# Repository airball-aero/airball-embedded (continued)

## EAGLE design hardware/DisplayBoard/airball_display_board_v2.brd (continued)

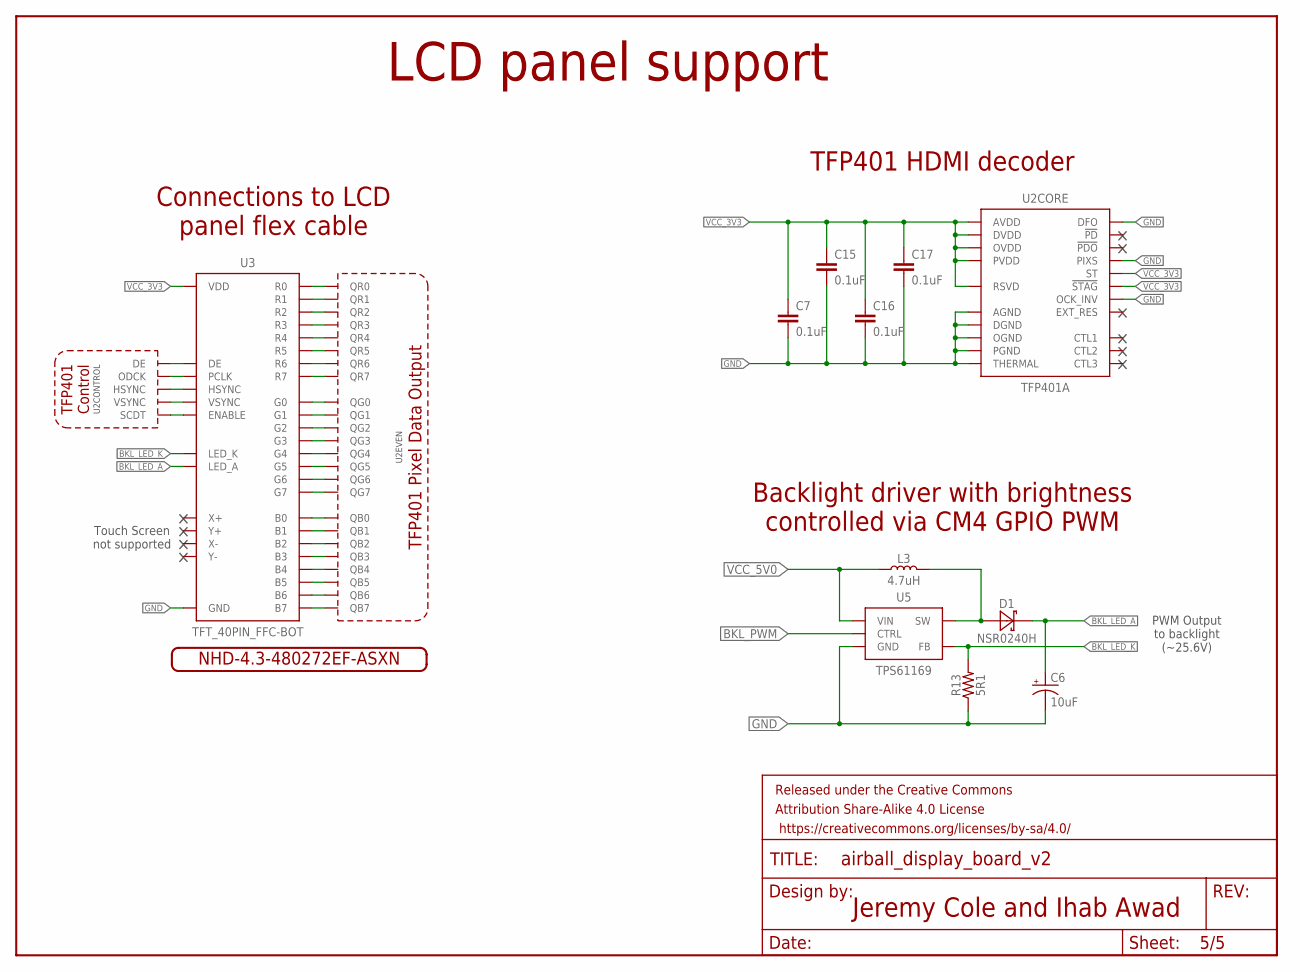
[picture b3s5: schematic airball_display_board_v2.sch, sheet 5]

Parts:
C6: 10uF; EIA3216
C7, C15, C16, C17: 0.1uF; 0603
D1: NSR0240H; SOD323
FRAME5: FRAME-LETTER; CREATIVE_COMMONS
L3: 4.7uH; INDUCTOR_SMD_4X4MM
R13: 5R1; 0603
U2: TFP401A; TQFP100_POWER_LITE
U3: TFT_40PIN_FFC-BOT; HIROSE_FFC40_FH12-40S-0.5SH
U5: TPS61169; SOT353-5
U$4: NHD-4.3-480272EF-ASXN

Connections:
B0: U2.10 (QB0), U3.21 (B0)
B1: U2.11 (QB1), U3.22 (B1)
B2: U2.12 (QB2), U3.23 (B2)
B3: U2.13 (QB3), U3.24 (B3)
B4: U2.14 (QB4), U3.25 (B4)
B5: U2.15 (QB5), U3.26 (B5)
B6: U2.16 (QB6), U3.27 (B6)
B7: U2.17 (QB7), U3.28 (B7)
BKL_LED_A: C6.+, D1.K (C), U3.2 (LED_A)
BKL_LED_K: R13.2, U3.1 (LED_K), U5.3 (FB)
BKL_PWM: U5.4 (CTRL); also elsewhere on the board
DE: U2.46 (DE), U3.34 (DE)
G0: U2.20 (QG0), U3.13 (G0)
G1: U2.21 (QG1), U3.14 (G1)
G2: U2.22 (QG2), U3.15 (G2)
G3: U2.23 (QG3), U3.16 (G3)
G4: U2.24 (QG4), U3.17 (G4)
G5: U2.25 (QG5), U3.18 (G5)
G6: U2.26 (QG6), U3.19 (G6)
G7: U2.27 (QG7), U3.20 (G7)
GND: C6.-, C7.2, C15.2, C16.2, C17.2, R13.1, U2.1 (DFO), U2.4 (PIXS), U2.5 (DGND), U2.19 (OGND), U2.28 (OGND), U2.39 (DGND), U2.45 (OGND), U2.58 (OGND), U2.68 (DGND), U2.76 (OGND), U2.79 (AGND), U2.83 (AGND), U2.87 (AGND), U2.89 (AGND), U2.92 (AGND), U2.98 (PGND), U2.100 (OCK_INV), U2.TH21 (THERMAL), U2.TH22 (THERMAL), U2.TH23 (THERMAL), U2.TH24 (THERMAL), U2.TH25 (THERMAL), U2.TH30 (THERMAL), U2.TH34 (THERMAL), U2.TH39 (THERMAL), U2.TH43 (THERMAL), U2.TH48 (THERMAL), U2.TH52 (THERMAL), U2.TH57 (THERMAL), U2.TH58 (THERMAL), U2.TH59 (THERMAL), U2.TH60 (THERMAL), U2.TH61 (THERMAL), U2.THA (THERMAL), U2.THB (THERMAL), U3.3 (GND), U3.29 (GND), U3.36 (GND), U5.2 (GND); also elsewhere on the board
HSYNC: U2.48 (HSYNC), U3.32 (HSYNC)
L_BKL: D1.A, L3.2, U5.1 (SW)
PCLK: U2.44 (ODCK), U3.30 (PCLK)
R0: U2.30 (QR0), U3.5 (R0)
R1: U2.31 (QR1), U3.6 (R1)
R2: U2.32 (QR2), U3.7 (R2)
R3: U2.33 (QR3), U3.8 (R3)
R4: U2.34 (QR4), U3.9 (R4)
R5: U2.35 (QR5), U3.10 (R5)
R6: U2.36 (QR6), U3.11 (R6)
R7: U2.37 (QR7), U3.12 (R7)
SCDT: U2.8 (SCDT), U3.31 (ENABLE)
VCC_3V3: C7.1, C15.1, C16.1, C17.1, U2.3 (ST), U2.6 (DVDD), U2.7 (!STAG), U2.18 (OVDD), U2.29 (OVDD), U2.38 (DVDD), U2.43 (OVDD), U2.57 (OVDD), U2.67 (DVDD), U2.78 (OVDD), U2.82 (AVDD), U2.84 (AVDD), U2.88 (AVDD), U2.95 (AVDD), U2.97 (PVDD), U2.99 (RSVD), U3.4 (VDD); also elsewhere on the board
VCC_5V0: L3.1, U5.5 (VIN); also elsewhere on the board
VSYNC: U2.47 (VSYNC), U3.33 (VSYNC)

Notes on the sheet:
Jeremy Cole and Ihab Awad
Touch Screen not supported
PWM Output to backlight (~25.6V)
LCD panel support
Connections to LCD panel flex cable
Backlight driver with brightness controlled via CM4 GPIO PWM
TFP401 HDMI decoder

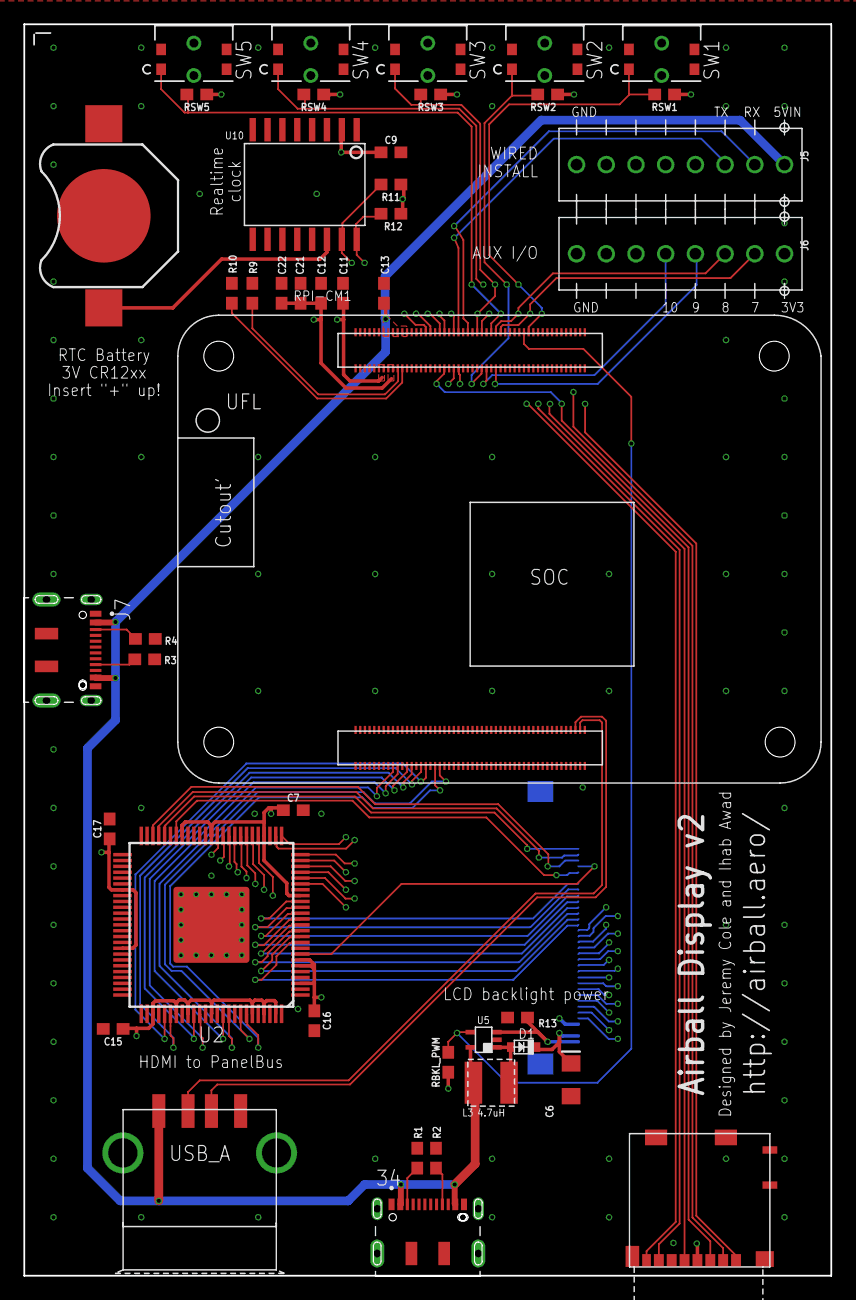
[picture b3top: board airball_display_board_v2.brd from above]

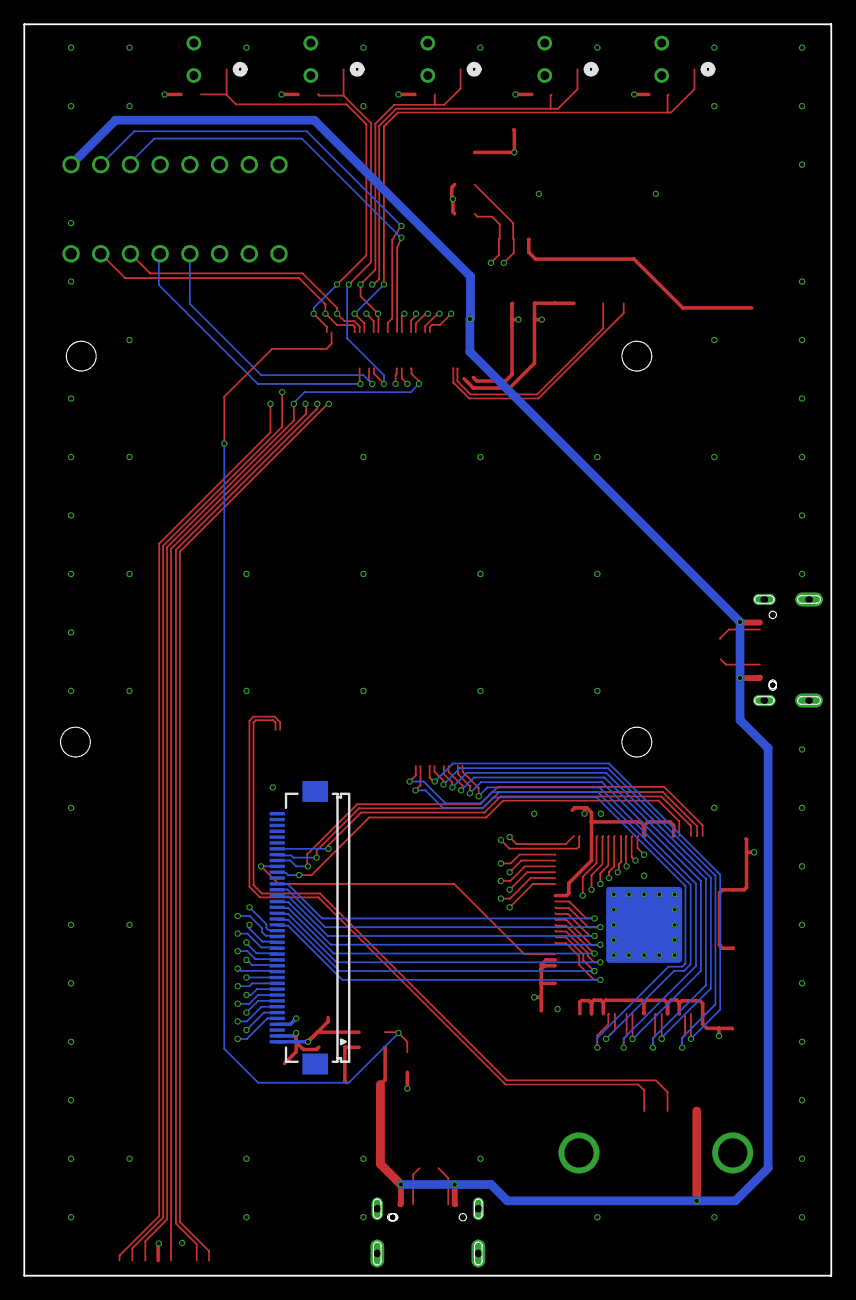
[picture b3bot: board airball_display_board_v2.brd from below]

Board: 4 copper layers, 69.0 x 107.0 mm, 51 parts (2 on the bottom side), 73 nets.

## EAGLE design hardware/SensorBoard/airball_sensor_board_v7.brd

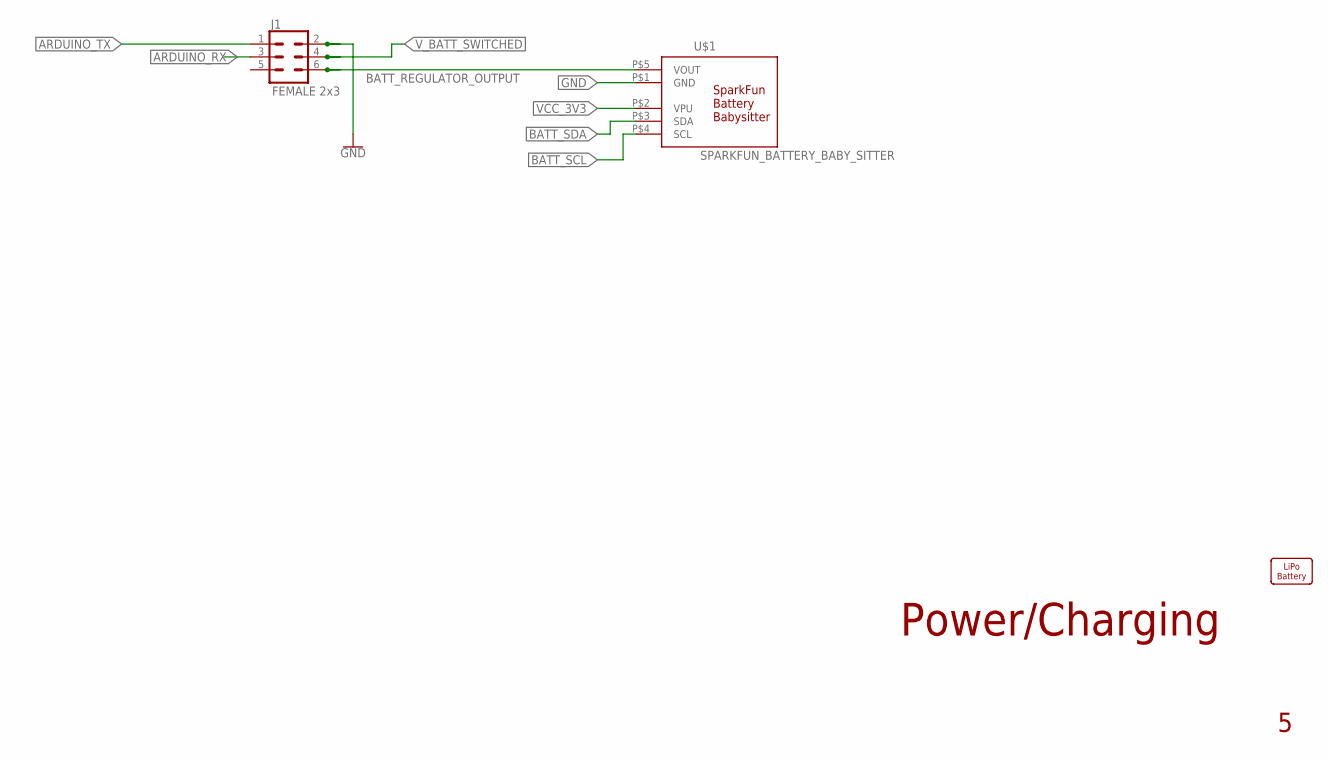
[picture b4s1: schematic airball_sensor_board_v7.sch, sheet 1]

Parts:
J1: FEMALE 2x3; 2X3
U$1: SPARKFUN_BATTERY_BABY_SITTER
U$3: LIPO_BATTERY_OUTLINE-1000MAH; SPARKFUN_LIPO_1000MAH

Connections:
ARDUINO_RX: J1.3; also elsewhere on the board
ARDUINO_TX: J1.1; also elsewhere on the board
BATT_REGULATOR_OUTPUT: J1.6, U$1.P$5 (VOUT)
BATT_SCL: U$1.P$4 (SCL); also elsewhere on the board
BATT_SDA: U$1.P$3 (SDA); also elsewhere on the board
GND: J1.2, U$1.P$1 (GND); also elsewhere on the board
VCC_3V3: U$1.P$2 (VPU); also elsewhere on the board
V_BATT_SWITCHED: J1.4; also elsewhere on the board

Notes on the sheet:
Power/Charging

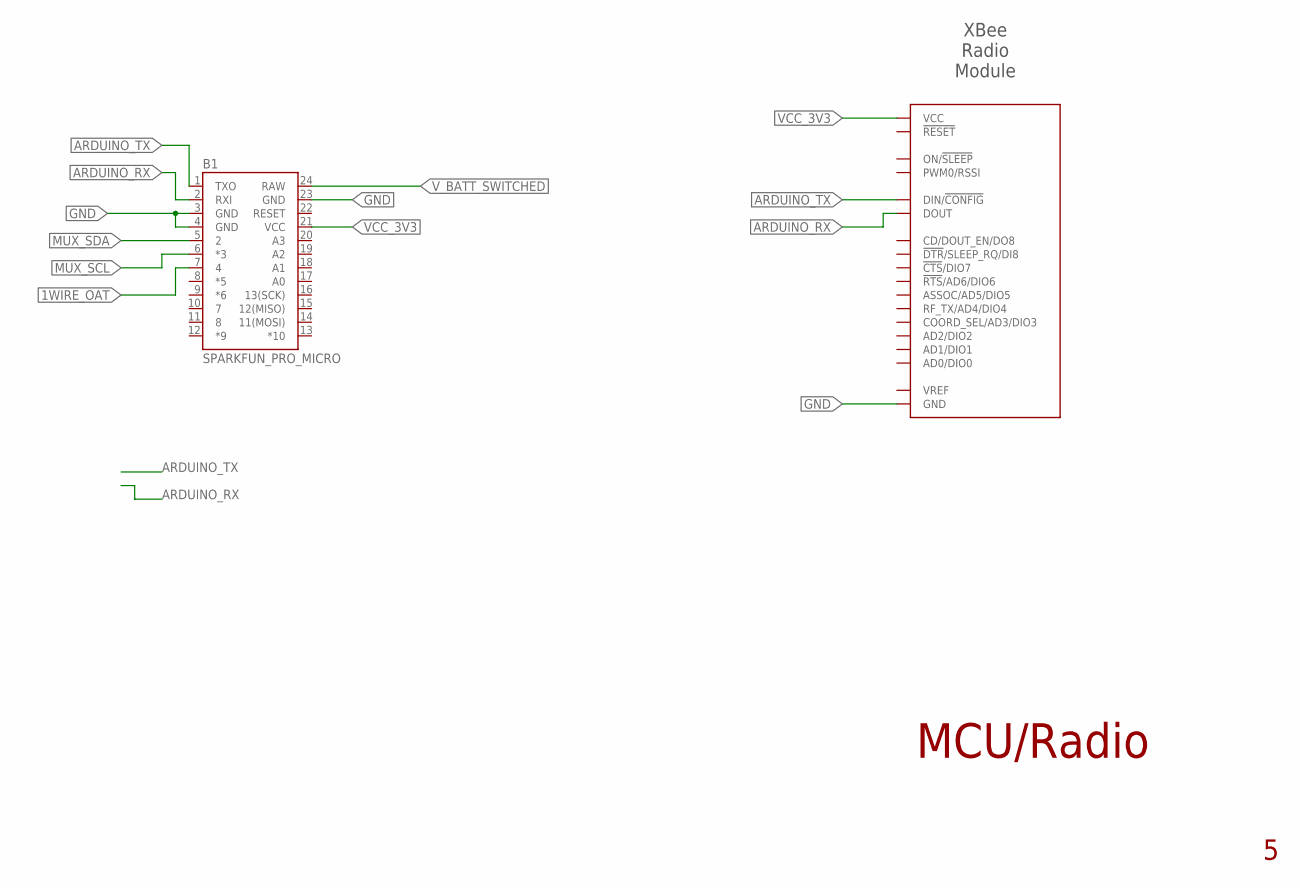
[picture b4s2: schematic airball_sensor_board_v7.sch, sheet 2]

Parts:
B1: SPARKFUN_PRO_MICRO
XBEE: XBEE-PRO-SMD

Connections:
1WIRE_OAT: B1.7 (4); also elsewhere on the board
ARDUINO_RX: B1.2 (RXI), XBEE.2 (DOUT); also elsewhere on the board
ARDUINO_TX: B1.1 (TXO), XBEE.3 (DIN/!CONFIG); also elsewhere on the board
GND: B1.3 (GND), B1.4 (GND), B1.23 (GND), XBEE.10 (GND); also elsewhere on the board
MUX_SCL: B1.6 (*3); also elsewhere on the board
MUX_SDA: B1.5 (2); also elsewhere on the board
VCC_3V3: B1.21 (VCC), XBEE.1 (VCC); also elsewhere on the board
V_BATT_SWITCHED: B1.24 (RAW); also elsewhere on the board

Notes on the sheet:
XBee Radio Module
MCU/Radio

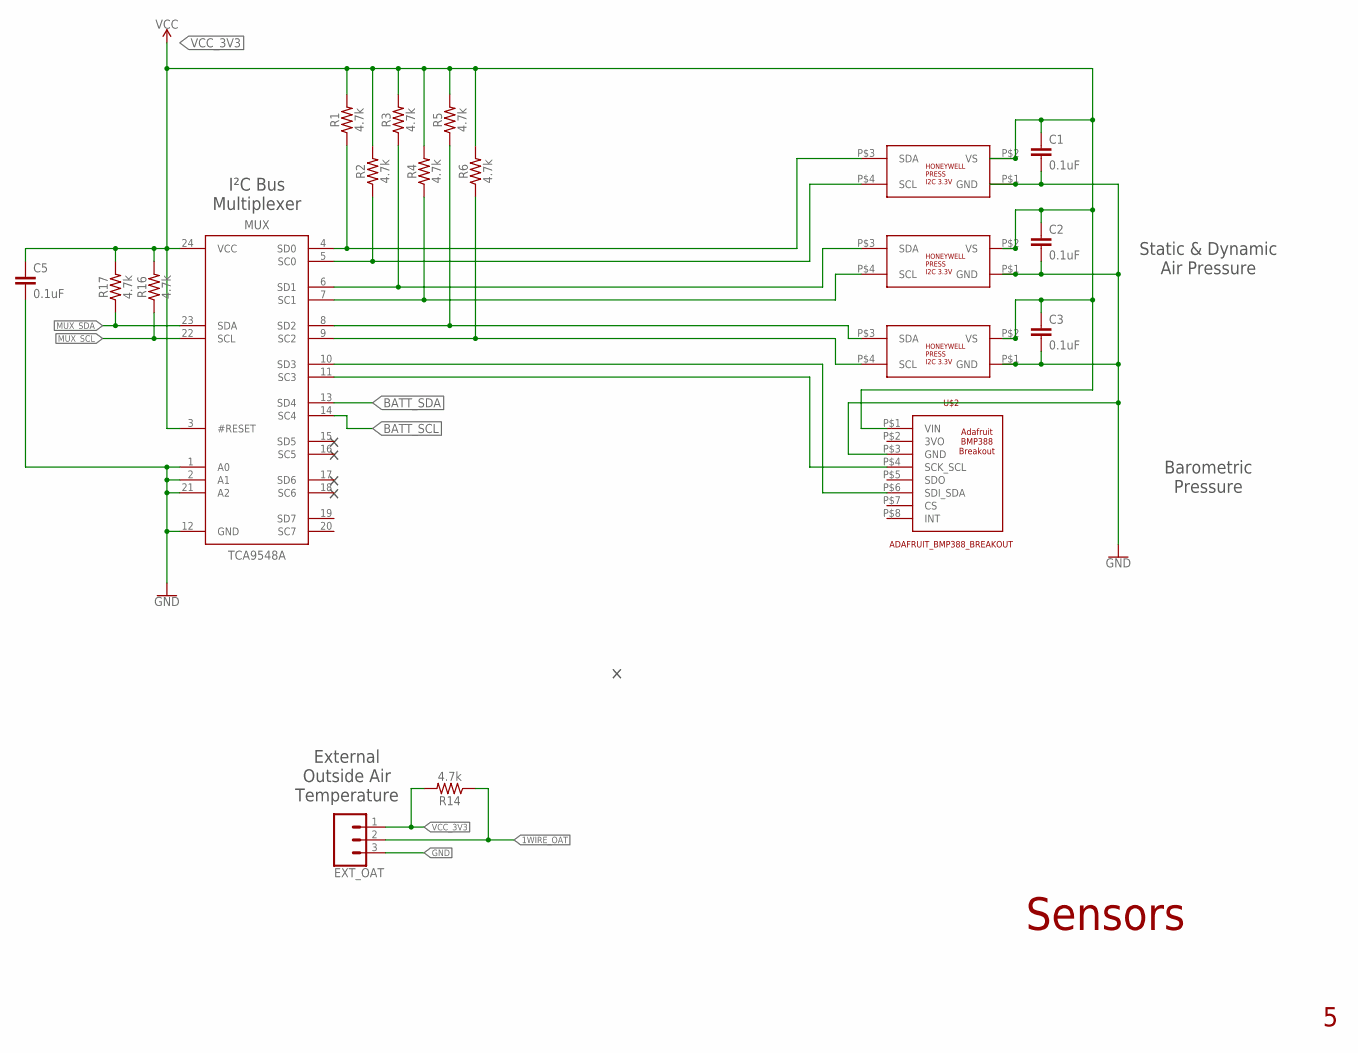
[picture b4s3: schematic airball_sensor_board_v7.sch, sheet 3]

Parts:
C1, C2, C3, C5: 0.1uF; 0603
DP0: HONEYWELL_TRUSTABILITY_I2C_3.3V; HONEYWELL_TRUSTABILITY_DIP_RR
DPA: HONEYWELL_TRUSTABILITY_I2C_3.3V; HONEYWELL_TRUSTABILITY_DIP_RR
DPB: HONEYWELL_TRUSTABILITY_I2C_3.3V; HONEYWELL_TRUSTABILITY_DIP_RR
EXT_OAT: CONN_03; 1X03
MUX: TCA9548A; TSSOP24
R1, R2, R3, R4, R5, R6, R14, R16, R17: 4.7k; 0603
U$2: ADAFRUIT_BMP388_BREAKOUT

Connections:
1WIRE_OAT: EXT_OAT.2, R14.1; also elsewhere on the board
BATT_SCL: MUX.14 (SC4); also elsewhere on the board
BATT_SDA: MUX.13 (SD4); also elsewhere on the board
GND: C1.2, C2.2, C3.2, C5.2, DP0.P$1 (GND), DPA.P$1 (GND), DPB.P$1 (GND), EXT_OAT.3, MUX.1 (A0), MUX.2 (A1), MUX.12 (GND), MUX.21 (A2), U$2.P$3 (GND); also elsewhere on the board
MUX_SCL: MUX.22 (SCL), R16.1; also elsewhere on the board
MUX_SDA: MUX.23 (SDA), R17.1; also elsewhere on the board
SCL_BMP_BARO: MUX.11 (SC3), U$2.P$4 (SCK_SCL)
SCL_DP0: DP0.P$4 (SCL), MUX.5 (SC0), R2.1
SCL_DPA: DPA.P$4 (SCL), MUX.7 (SC1), R4.1
SCL_DPB: DPB.P$4 (SCL), MUX.9 (SC2), R6.1
SDA_BMP_BARO: MUX.10 (SD3), U$2.P$6 (SDI_SDA)
SDA_DP0: DP0.P$3 (SDA), MUX.4 (SD0), R1.1
SDA_DPA: DPA.P$3 (SDA), MUX.6 (SD1), R3.1
SDA_DPB: DPB.P$3 (SDA), MUX.8 (SD2), R5.1
VCC_3V3: C1.1, C2.1, C3.1, C5.1, DP0.P$2 (VS), DPA.P$2 (VS), DPB.P$2 (VS), EXT_OAT.1, MUX.3 (#RESET), MUX.24 (VCC), R1.2, R2.2, R3.2, R4.2, R5.2, R6.2, R14.2, R16.2, R17.2, U$2.P$1 (VIN); also elsewhere on the board

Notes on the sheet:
Sensors
I²C Bus Multiplexer
Static & Dynamic Air Pressure
External Outside Air Temperature
Barometric Pressure

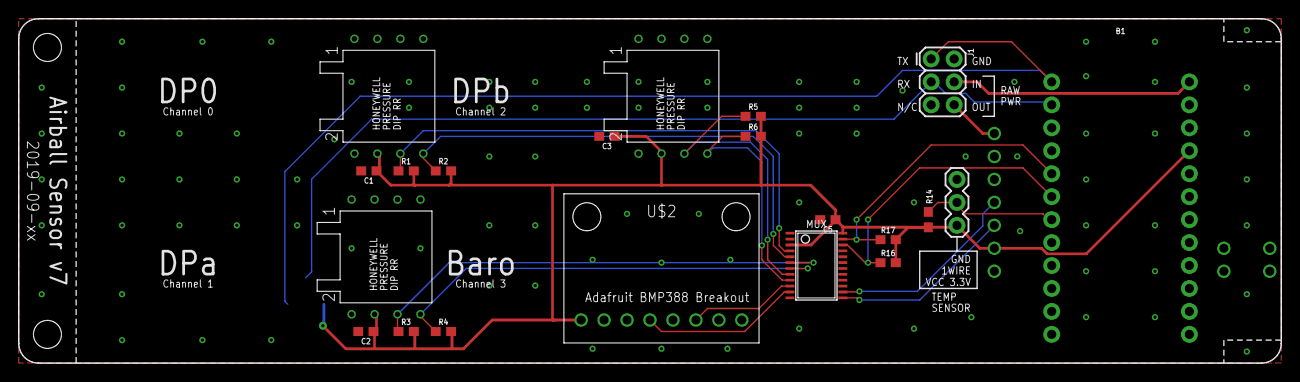
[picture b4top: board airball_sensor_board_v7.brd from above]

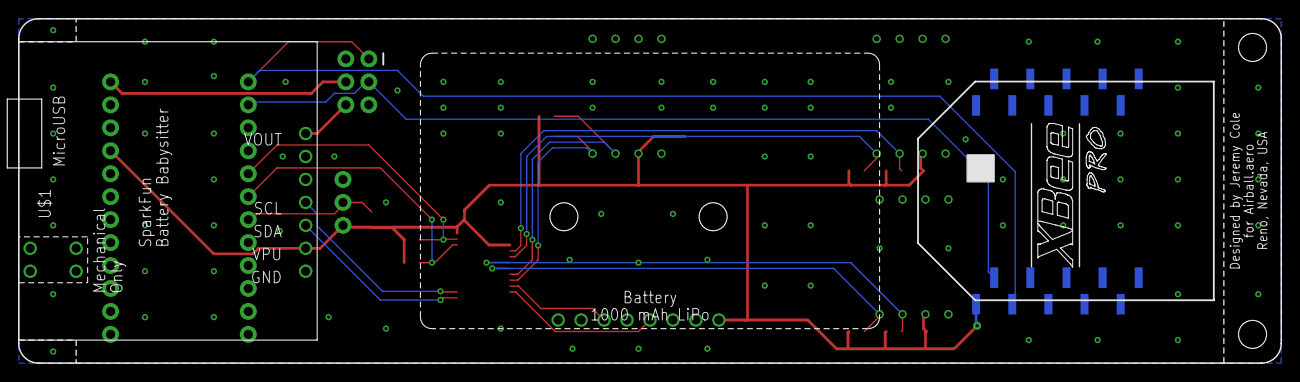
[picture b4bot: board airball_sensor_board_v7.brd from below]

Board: 2 copper layers, 139.7 x 38.1 mm, 24 parts (3 on the bottom side), 19 nets.

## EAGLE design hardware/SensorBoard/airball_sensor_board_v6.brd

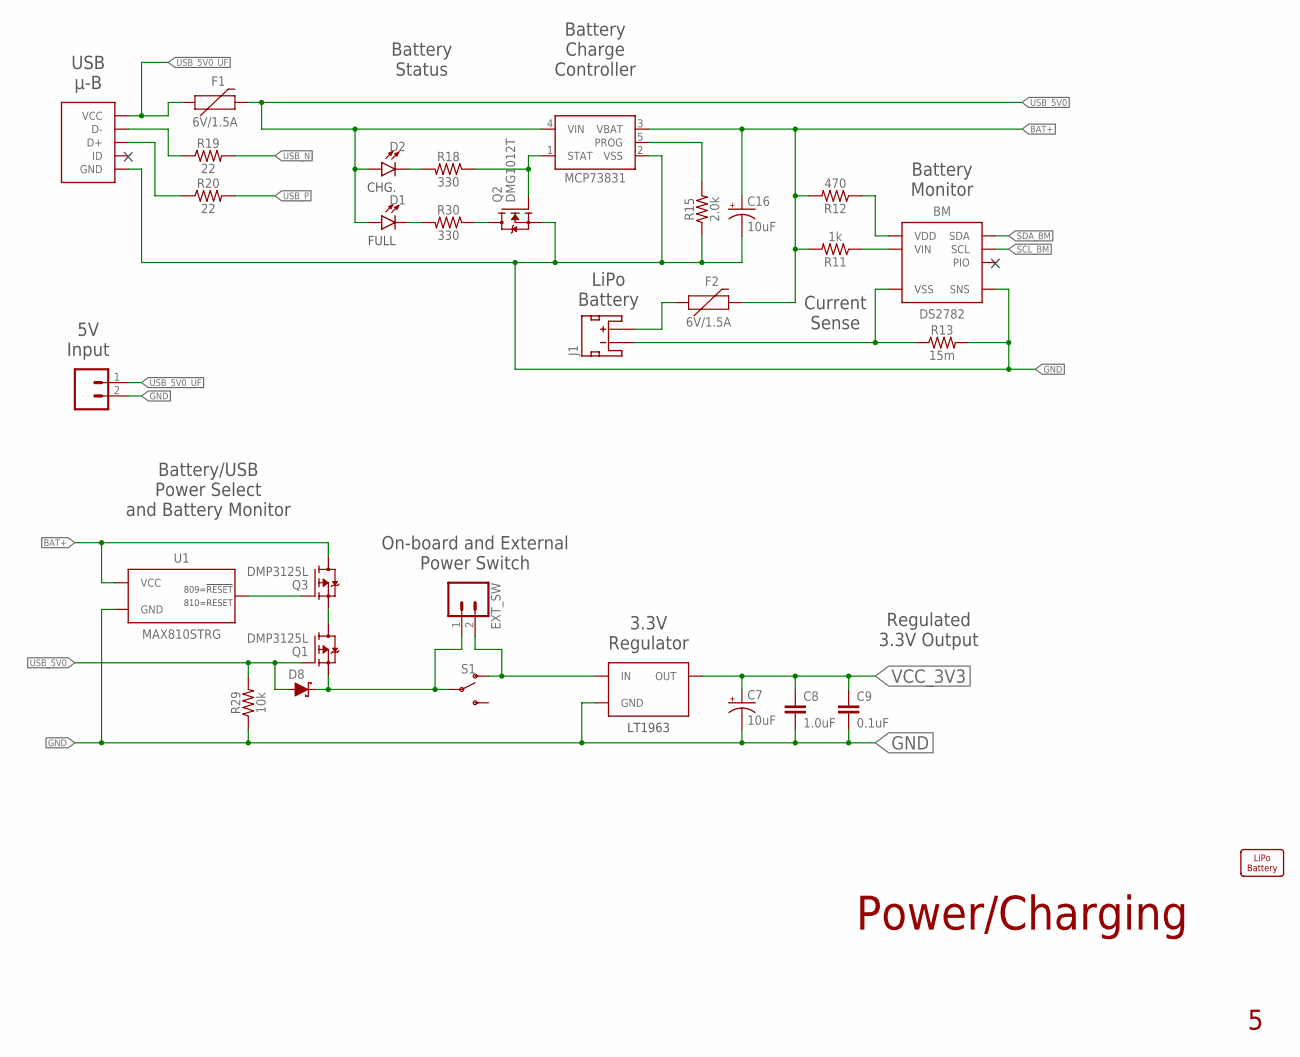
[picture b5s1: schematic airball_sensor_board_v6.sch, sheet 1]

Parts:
BM: DS2782; TSSOP8
C7, C16: 10uF; EIA3216
C8: 1.0uF; 0603
C9: 0.1uF; 0603
CC: MCP73831; SOT23-5
D1, D2: LED0603; LED-0603
D8: DIODE-SCHOTTKY-BAT20J; SOD-323
EXT_POWER: CONN_02; 1X02
EXT_SW: CONN_02; 1X02
F1, F2: 6V/1.5A; 1206
J1: JST_2MM_MALE; JST-2-SMD
JP1: USB_MICROB_PLUG; USB_MICRO_B_TYCO
Q1, Q3: DMP3125L; SOT23-3
Q2: DMG1012T; SOT523-3
R11: 1k; 0603
R12: 470; 0603
R13: 15m; 1206
R15: 2.0k; 0603
R18, R30: 330; 0603
R19, R20: 22; 0603
R29: 10k; 0603
S1: SWITCH-SPDT-SMD-RIGHT-ANGLE; SWITCH_SPST_SMD_A
U1: MAX810STRG; SOT23-3
U$3: LIPO_BATTERY_OUTLINE-1000MAH; SPARKFUN_LIPO_1000MAH
VREG: LT1963; SOT223-3

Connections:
BAT+: C16.+, CC.3 (VBAT), F2.2, Q3.3 (D), R11.2, R12.2, U1.3 (VCC)
BAT+_UF: F2.1, J1.2 (+)
BAT-: BM.2 (VSS), J1.1 (-), R13.1
BAT_LOW: Q3.1 (G), U1.2 (RESET)
BM_VDD: BM.4 (VDD), R12.1
BM_VIN: BM.3 (VIN), R11.1
CC_PROG: CC.5 (PROG), R15.2
GND: BM.7 (SNS), C7.-, C8.2, C9.2, C16.-, CC.2 (VSS), EXT_POWER.2, JP1.5 (GND), JP1.SH@1 (GND), JP1.SH@2 (GND), JP1.SH@3 (GND), JP1.SH@4 (GND), Q2.3 (S), R13.2, R15.1, R29.1, U1.1 (GND), VREG.2 (GND), VREG.TAB (GND); also elsewhere on the board
unnamed: D2.C, R18.2
unnamed: CC.1 (STAT), Q2.1 (G), R18.1
unnamed: Q1.3 (D), Q3.2 (S)
unnamed: D1.C, R30.2
unnamed: Q2.2 (D), R30.1
SCL_BM: BM.6 (SCL); also elsewhere on the board
SDA_BM: BM.5 (SDA); also elsewhere on the board
USB_5V0: CC.4 (VIN), D1.A, D2.A, D8.A, F1.2, Q1.1 (G), R29.2
USB_5V0_UF: EXT_POWER.1, F1.1, JP1.1 (VCC)
USB_N: R19.2; also elsewhere on the board
USB_P: R20.2; also elsewhere on the board
USB_X_N: JP1.2 (D-), R19.1
USB_X_P: JP1.3 (D+), R20.1
VCC_3V3: C7.+, C8.1, C9.1, VREG.3 (OUT); also elsewhere on the board
VIN: D8.C, EXT_SW.1, Q1.2 (S), S1.2
VIN_SW: EXT_SW.2, S1.1 (O), VREG.1 (IN)

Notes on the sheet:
LiPo Battery
USB µ-B
Battery Monitor
3.3V Regulator
Battery Charge Controller
On-board and External Power Switch
Regulated 3.3V Output
Battery Status
Current Sense
Power/Charging
5V Input
CHG.
FULL
Battery/USB Power Select and Battery Monitor

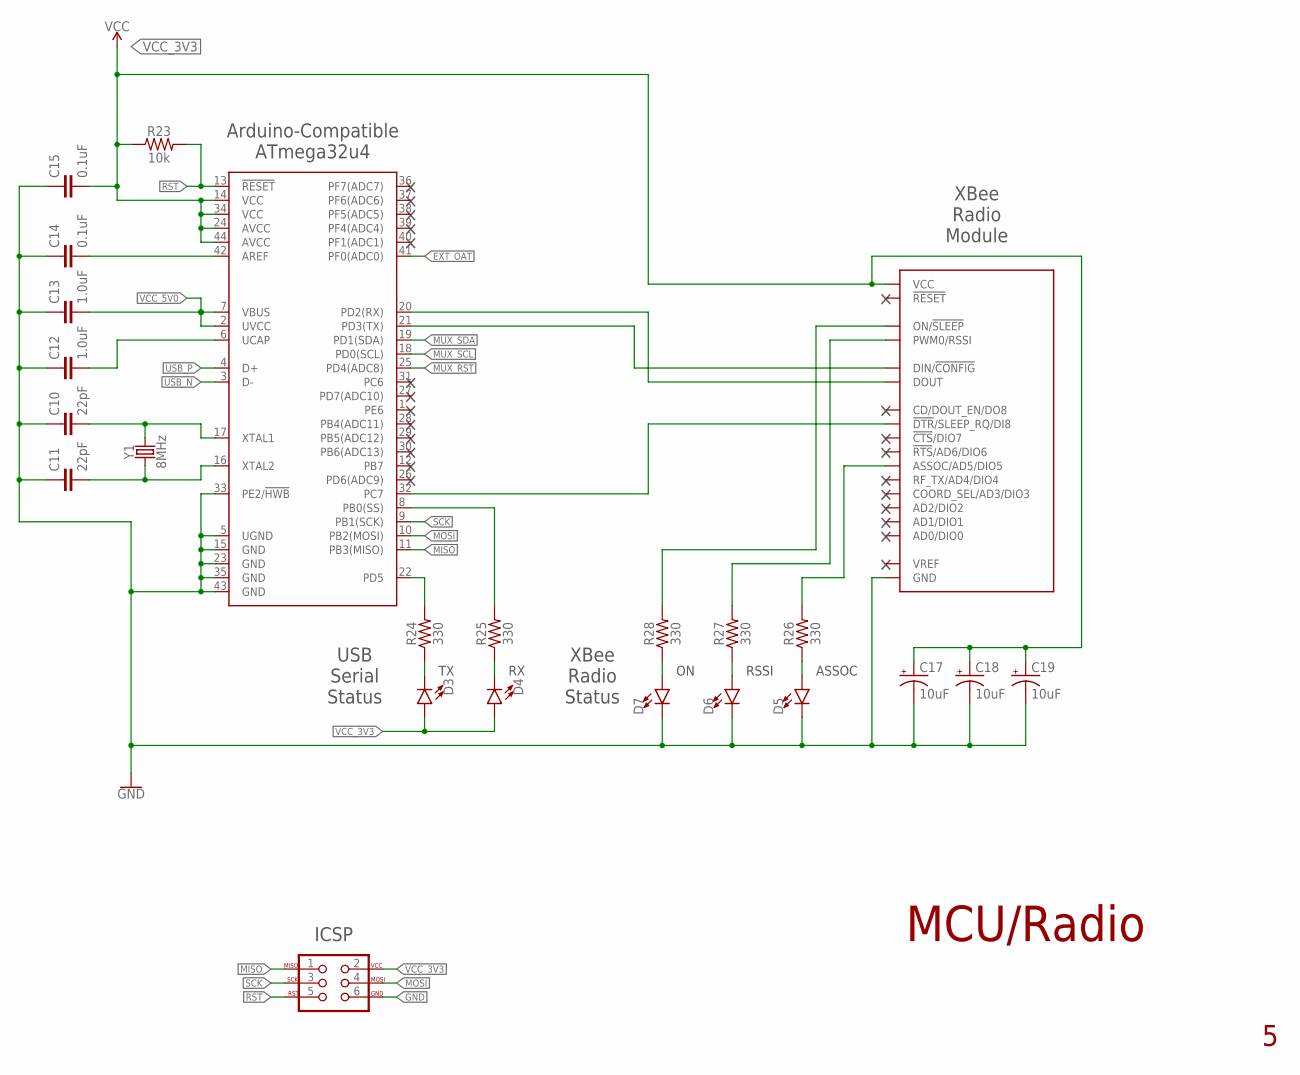
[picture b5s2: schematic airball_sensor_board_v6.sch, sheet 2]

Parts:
C10, C11: 22pF; 0603
C12, C13: 1.0uF; 0603
C14, C15: 0.1uF; 0603
C17, C18, C19: 10uF; EIA3216
D3, D4, D5, D6, D7: LED0603; LED-0603
ICSP: AVR_SPI_PROG_3X2PTH; 2X3
MCU: 32U4; TQFP44
R23: 10k; 0603
R24, R25, R26, R27, R28: 330; 0603
XBEE: XBEE-PRO-SMD
Y1: 8MHz; CRYSTAL-SMD-5X3.2-4PAD

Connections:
ASSOC_LED: R26.2, XBEE.15 (ASSOC/AD5/DIO5)
EXT_OAT: MCU.41 (PF0(ADC0)); also elsewhere on the board
GND: C10.1, C11.1, C12.1, C13.1, C14.1, C15.1, C17.-, C18.-, C19.-, D5.C, D6.C, D7.C, ICSP.6, MCU.5 (UGND), MCU.15 (GND), MCU.23 (GND), MCU.33 (PE2/!HWB), MCU.35 (GND), MCU.43 (GND), XBEE.10 (GND); also elsewhere on the board
MISO: ICSP.1, MCU.11 (PB3(MISO))
MOSI: ICSP.4, MCU.10 (PB2(MOSI))
MUX_RST: MCU.25 (PD4(ADC8)); also elsewhere on the board
MUX_SCL: MCU.18 (PD0(SCL)); also elsewhere on the board
MUX_SDA: MCU.19 (PD1(SDA)); also elsewhere on the board
unnamed: D3.C, R24.1
unnamed: D4.C, R25.1
unnamed: C10.2, MCU.17 (XTAL1), Y1.3 (2)
unnamed: C11.2, MCU.16 (XTAL2), Y1.1
unnamed: C14.2, MCU.42 (AREF)
unnamed: C12.2, MCU.6 (UCAP)
unnamed: D5.A, R26.1
unnamed: D6.A, R27.1
unnamed: D7.A, R28.1
ON_LED: R28.2, XBEE.13 (ON/!SLEEP)
RSSI_LED: R27.2, XBEE.6 (PWM0/RSSI)
RST: ICSP.5, MCU.13 (!RESET), R23.2
RXD: MCU.20 (PD2(RX)), XBEE.2 (DOUT)
RX_LED: MCU.8 (PB0(SS)), R25.2
SCK: ICSP.3, MCU.9 (PB1(SCK))
SLEEP_RQ: MCU.32 (PC7), XBEE.9 (!DTR!/SLEEP_RQ/DI8)
TXD: MCU.21 (PD3(TX)), XBEE.3 (DIN/!CONFIG)
TX_LED: MCU.22 (PD5), R24.2
USB_N: MCU.3 (D-); also elsewhere on the board
USB_P: MCU.4 (D+); also elsewhere on the board
VCC_3V3: C15.2, C17.+, C18.+, C19.+, D3.A, D4.A, ICSP.2, MCU.14 (VCC), MCU.24 (AVCC), MCU.34 (VCC), MCU.44 (AVCC), R23.1, XBEE.1 (VCC); also elsewhere on the board
VCC_5V0: C13.2, MCU.2 (UVCC), MCU.7 (VBUS)

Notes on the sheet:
RSSI
ASSOC
XBee Radio Module
Arduino-Compatible ATmega32u4
ICSP
USB Serial Status
XBee Radio Status
MCU/Radio

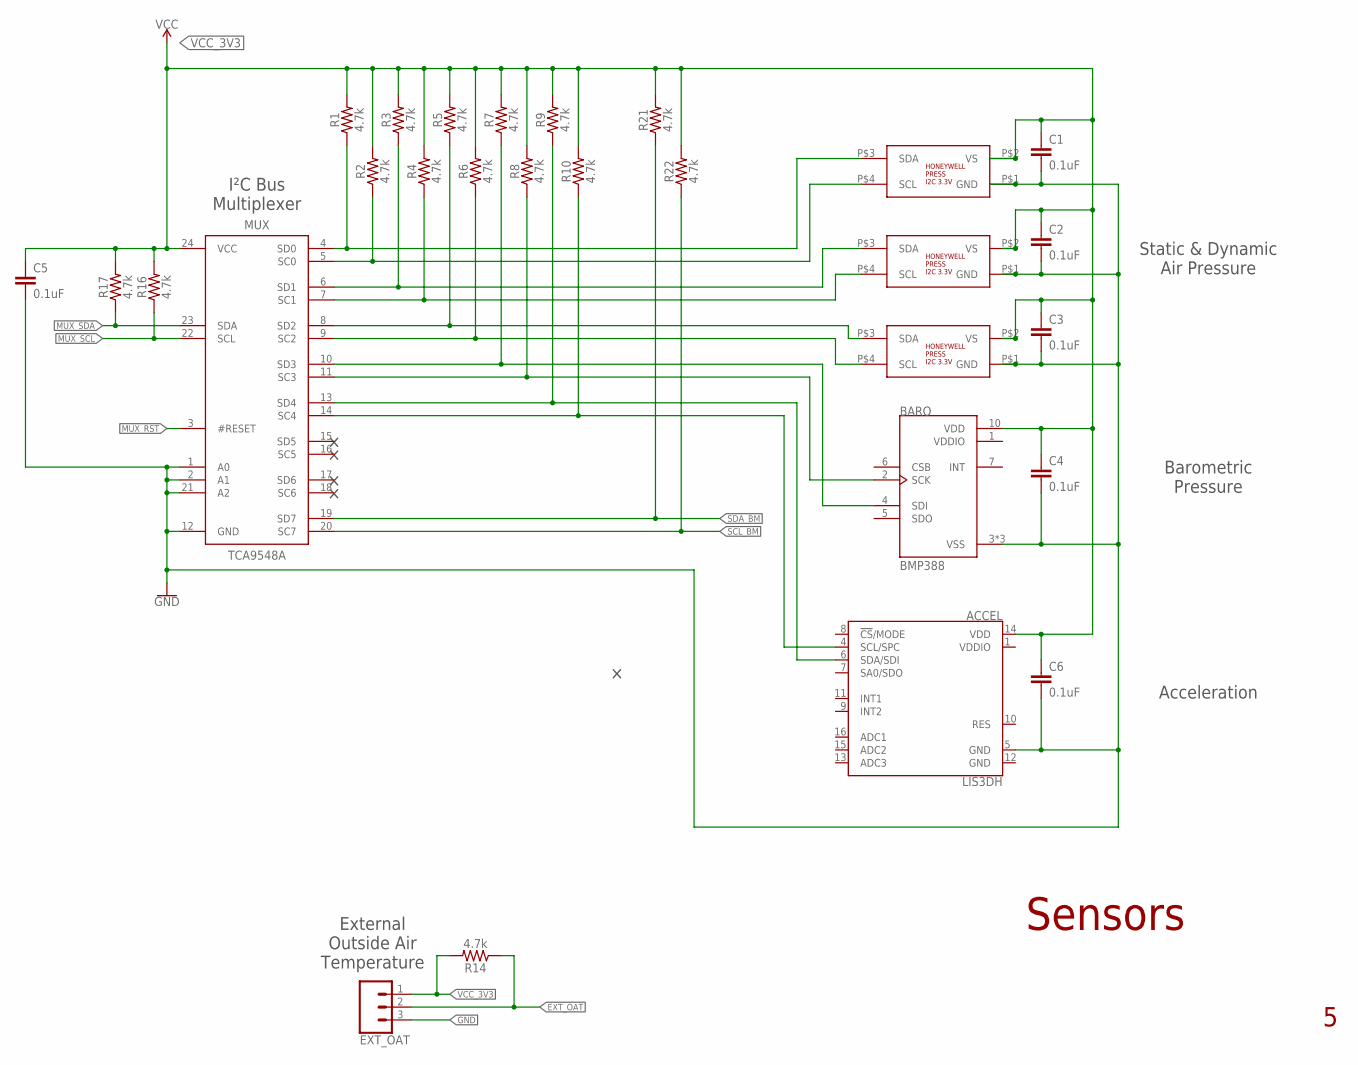
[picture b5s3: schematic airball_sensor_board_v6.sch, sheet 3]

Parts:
ACCEL: LIS3DH; LGA-16-3X3
BARO: BMP388; PQFN50P200X200X80-10N
C1, C2, C3, C4, C5, C6: 0.1uF; 0603
DP0: HONEYWELL_TRUSTABILITY_I2C_3.3V; HONEYWELL_TRUSTABILITY_DIP_RR
DPA: HONEYWELL_TRUSTABILITY_I2C_3.3V; HONEYWELL_TRUSTABILITY_DIP_RR
DPB: HONEYWELL_TRUSTABILITY_I2C_3.3V; HONEYWELL_TRUSTABILITY_DIP_RR
EXT_OAT: CONN_03; 1X03
MUX: TCA9548A; TSSOP24
R1, R2, R3, R4, R5, R6, R7, R8, R9, R10, R14, R16, R17, R21, R22: 4.7k; 0603

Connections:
EXT_OAT: EXT_OAT.2, R14.1; also elsewhere on the board
GND: ACCEL.5 (GND), BARO.3 (VSS), BARO.8 (VSS), BARO.9 (VSS), C1.2, C2.2, C3.2, C4.2, C5.2, C6.2, DP0.P$1 (GND), DPA.P$1 (GND), DPB.P$1 (GND), EXT_OAT.3, MUX.1 (A0), MUX.2 (A1), MUX.12 (GND), MUX.21 (A2); also elsewhere on the board
MUX_RST: MUX.3 (#RESET); also elsewhere on the board
MUX_SCL: MUX.22 (SCL), R16.1; also elsewhere on the board
MUX_SDA: MUX.23 (SDA), R17.1; also elsewhere on the board
SCL_ACCEL: ACCEL.4 (SCL/SPC), MUX.14 (SC4), R10.1
SCL_BM: MUX.20 (SC7), R22.1; also elsewhere on the board
SCL_BMP_BARO: BARO.2 (SCK), MUX.11 (SC3), R8.1
SCL_DP0: DP0.P$4 (SCL), MUX.5 (SC0), R2.1
SCL_DPA: DPA.P$4 (SCL), MUX.7 (SC1), R4.1
SCL_DPB: DPB.P$4 (SCL), MUX.9 (SC2), R6.1
SDA_ACCEL: ACCEL.6 (SDA/SDI), MUX.13 (SD4), R9.1
SDA_BM: MUX.19 (SD7), R21.1; also elsewhere on the board
SDA_BMP_BARO: BARO.4 (SDI), MUX.10 (SD3), R7.1
SDA_DP0: DP0.P$3 (SDA), MUX.4 (SD0), R1.1
SDA_DPA: DPA.P$3 (SDA), MUX.6 (SD1), R3.1
SDA_DPB: DPB.P$3 (SDA), MUX.8 (SD2), R5.1
VCC_3V3: ACCEL.14 (VDD), BARO.10 (VDD), C1.1, C2.1, C3.1, C4.1, C5.1, C6.1, DP0.P$2 (VS), DPA.P$2 (VS), DPB.P$2 (VS), EXT_OAT.1, MUX.24 (VCC), R1.2, R2.2, R3.2, R4.2, R5.2, R6.2, R7.2, R8.2, R9.2, R10.2, R14.2, R16.2, R17.2, R21.2, R22.2; also elsewhere on the board
VDDIO: BARO.1 (VDDIO)

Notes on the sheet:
Sensors
I²C Bus Multiplexer
Static & Dynamic Air Pressure
External Outside Air Temperature
Barometric Pressure
Acceleration
